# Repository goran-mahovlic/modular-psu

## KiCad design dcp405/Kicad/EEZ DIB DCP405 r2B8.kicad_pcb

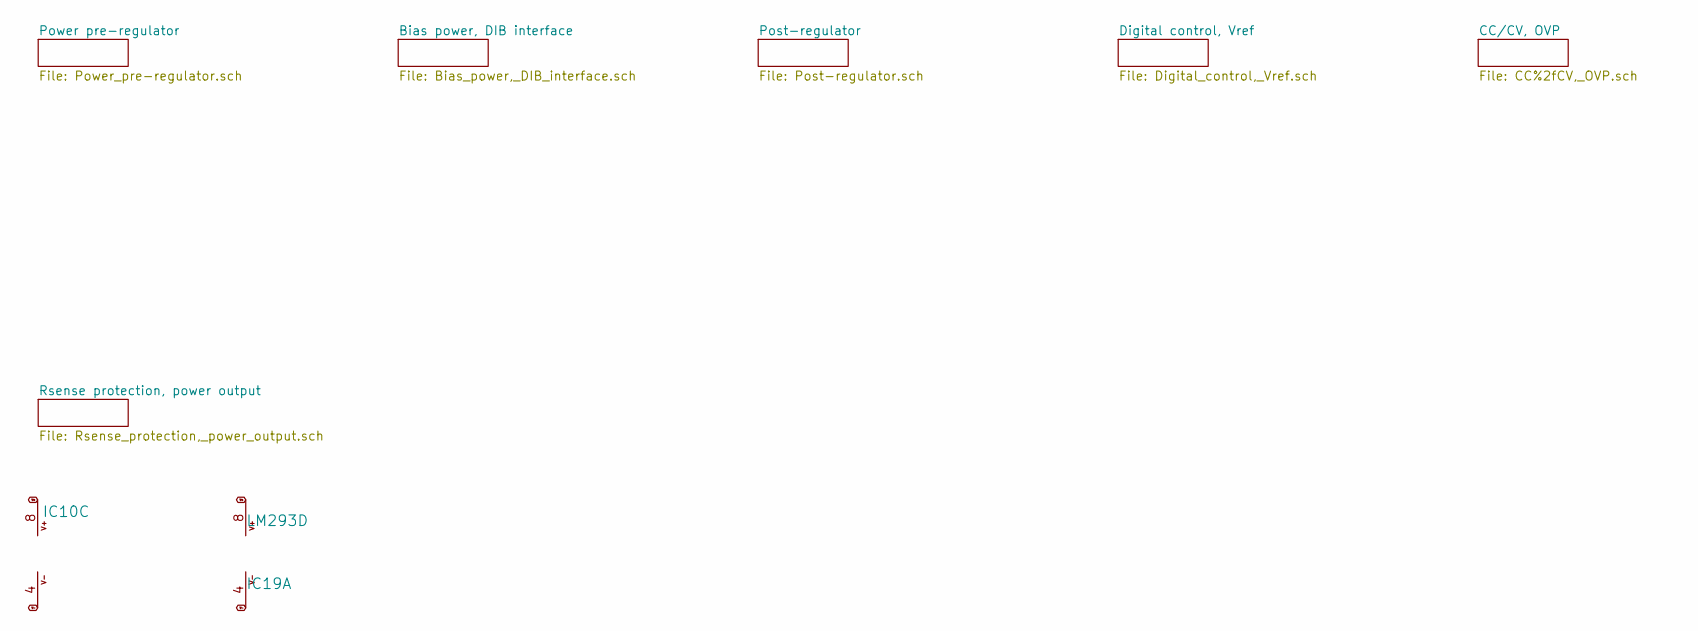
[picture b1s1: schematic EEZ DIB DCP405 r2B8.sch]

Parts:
IC10: MC33272ADR2G; SOIC127P600X173-8N
IC19: LM293D; SOIC127P600X173-8N

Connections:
V+: IC10.8 (V+), IC19.8 (V+); also elsewhere on the board
V-: IC10.4 (V-), IC19.4 (V-); also elsewhere on the board

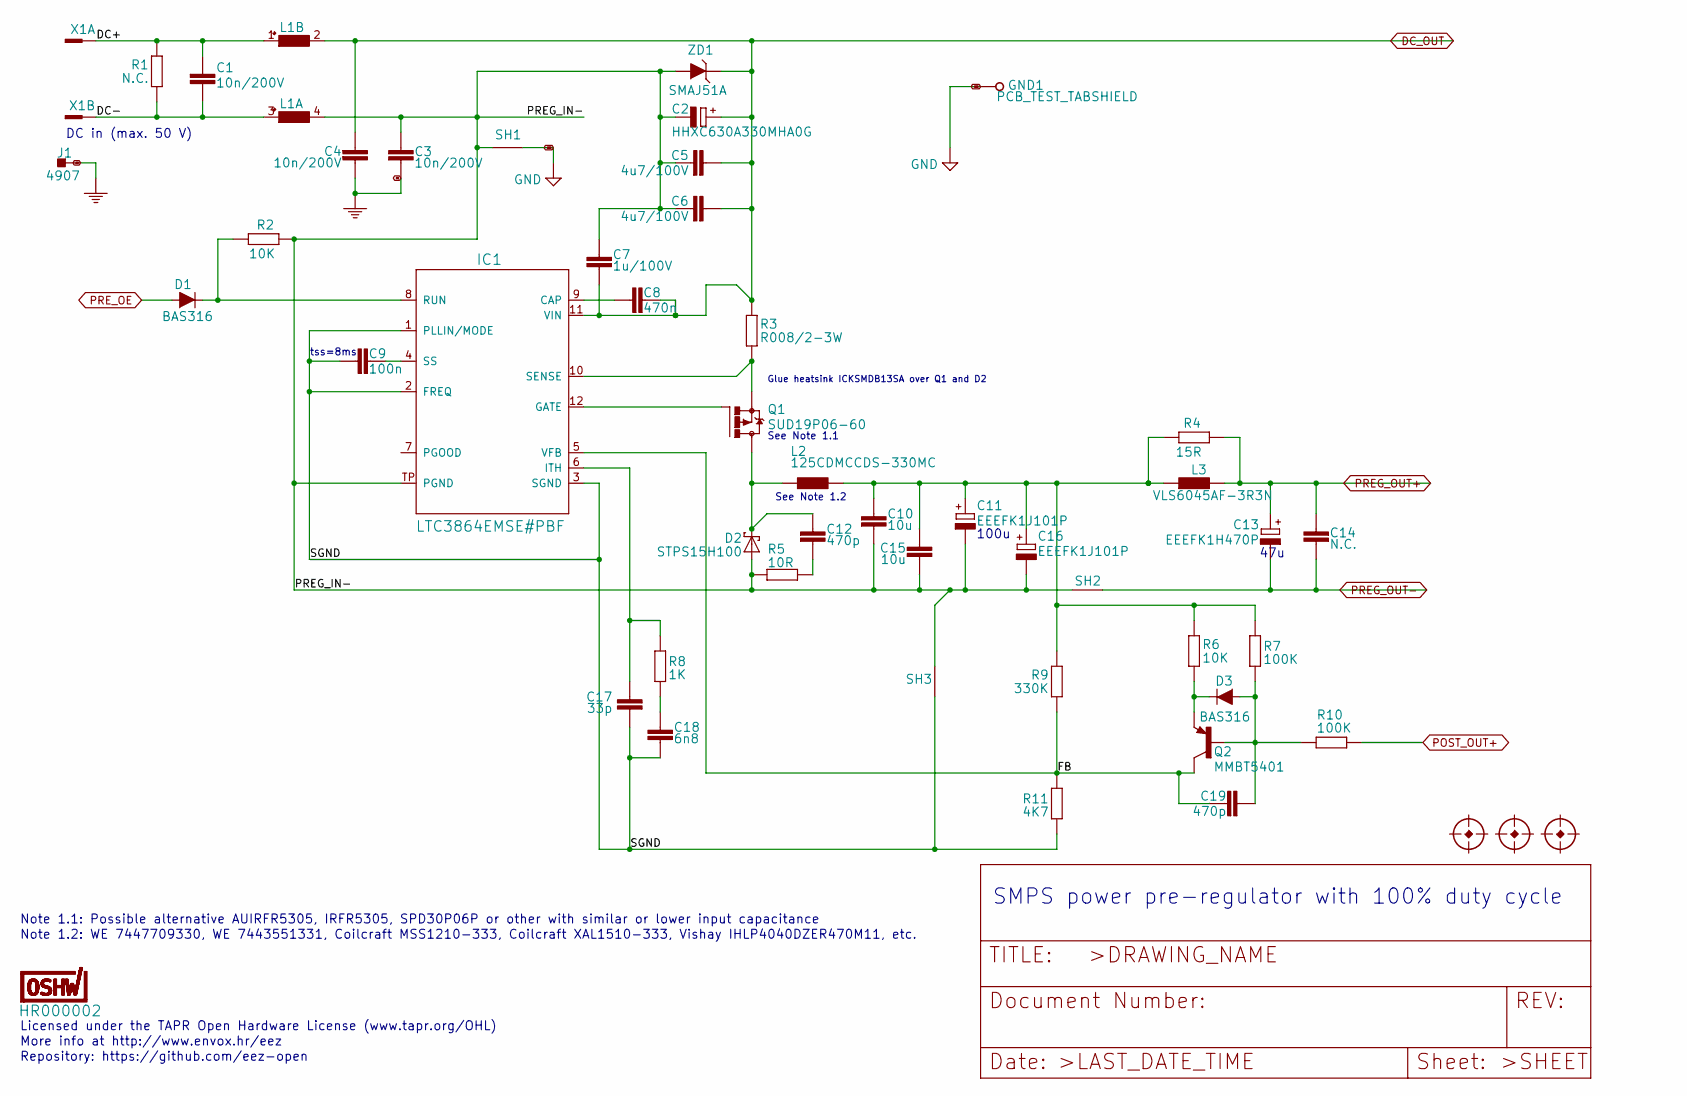
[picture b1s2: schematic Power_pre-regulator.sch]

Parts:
C1, C3, C4: 10n/200V; C1206
C2: HHXC630A330MHA0G; CAPAE830X1050N
C5, C6: 4u7/100V; C1210
C7: 1u/100V; C1206
C8: 470n; C0805
C9: 100n; C0603
C10, C15: 10u; C1210
C11, C16: EEEFK1J101P; CAPAE1030X1050N
C12, C19: 470p; C0805
C13: EEEFK1H470P; CAPAE830X1050N
C14: N.C.; C0805
C17: 33p; C0805
C18: 6n8; C0805
D1, D3: BAS316; SOD323-R
D2: STPS15H100; TO252-L
FM1, FM2, FM3: FIDUCIAL_2; FIDUCIAL_DUAL
GND: PCB_TEST_TABSHIELD; PCB_SHIELD_TAB
IC1: LTC3864EMSE#PBF; LTC_05-08-1666
J1: 4907; PCB_TAB-4907
L1: RN112-4-02-0M7; RN112
L2: 125CDMCCDS-330MC; 125CDMCC_DS
L3: VLS6045AF-3R3N; COILCRAFT_HPI0630
OSHWA: HR000002; CERT-SMALL-SILK
Q1: SUD19P06-60; TO229P990X239-3N
Q2: MMBT5401; SOT23-BEC
R1: N.C.; R2512
R2, R6: 10K; R0805
R3: R008/2-3W; R2512
R4: 15R; R2010
R5: 10R; R1206
R7, R10: 100K; R0805
R8: 1K; R0805
R9: 330K; R0805
R11: 4K7; R0805
SH1: SHORTNOHOLE; SHORT_NOHOLE
SH2: Pgnd to Pout- short; SHORT_NOHOLE
SH3: Sgnd to Pgnd short; SHORT_NOHOLE
X1: 39-30-1020; MINIFIT_39301020
ZD1: SMAJ51A; DO214AA

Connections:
/Power pre-regulator/DC+: C1.2, L1.1, R1.2, X1.1
/Power pre-regulator/DC-: C1.1, L1.3 (1), R1.1, X1.2
/Power pre-regulator/FB: C19.1, IC1.5 (VFB), Q2.C, R9.2, R11.1
/Power pre-regulator/PREG_IN-: C2.-, C3.1, C5.2, C6.2, C7.2, C10.2, C11.-, C15.2, C16.-, D2.1 (A), D2.2 (A), IC1.TP (PGND), L1.4 (2), R2.1, R5.1, SH1.1 (GND_A), SH2.2 (GND_B), SH3.2 (GND_B), ZD1.A
/Power pre-regulator/SGND: C9.1, C17.2, C18.2, IC1.1 (PLLIN/MODE), IC1.2 (FREQ), IC1.3 (SGND), R11.2, SH3.1 (GND_A)
DC_OUT: C2.+, C4.2, C5.1, C6.1, C7.1, C8.2, IC1.11 (VIN), L1.2, R3.1, ZD1.C; also elsewhere on the board
GND: GND.1, SH1.2 (GND_B); also elsewhere on the board
unnamed: C8.1, IC1.9 (CAP)
unnamed: C9.2, IC1.4 (SS)
unnamed: C10.1, C11.+, C15.1, C16.+, L2.2, L3.1, R4.1, R6.1, R7.1, R9.1
unnamed: C12.1, D2.3 (C), L2.1, Q1.2 (D)
unnamed: C12.2, R5.2
unnamed: C17.1, IC1.6 (ITH), R8.2
unnamed: C18.1, R8.1
unnamed: C19.2, D3.A, Q2.B, R7.2, R10.1
unnamed: D1.C, IC1.8 (RUN), R2.2
unnamed: D3.C, Q2.E, R6.2
unnamed: IC1.10 (SENSE), Q1.3 (S), R3.2
unnamed: IC1.12 (GATE), Q1.1 (G)
PE: C3.2, C4.1, J1.1, J1.2; also elsewhere on the board
POST_OUT+: R10.2; also elsewhere on the board
PREG_OUT+: C13.+, C14.1, L3.2, R4.2; also elsewhere on the board
PREG_OUT-: C13.-, C14.2, SH2.1 (GND_A); also elsewhere on the board
PRE_OE: D1.A; also elsewhere on the board

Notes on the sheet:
47u
tss=8ms
Licensed under the TAPR Open Hardware License (www.tapr.org/OHL)
Repository: https://github.com/eez-open
More info at http://www.envox.hr/eez
SMPS power pre-regulator with 100% duty cycle
100u
See Note 1.1
Note 1.1: Possible alternative AUIRFR5305, IRFR5305, SPD30P06P or other with similar or lower input capacitance
Note 1.2: WE 7447709330, WE 7443551331, Coilcraft MSS1210-333, Coilcraft XAL1510-333, Vishay IHLP4040DZER470M11, etc.
DC in (max. 50 V)
See Note 1.2
Glue heatsink ICKSMDB13SA over Q1 and D2

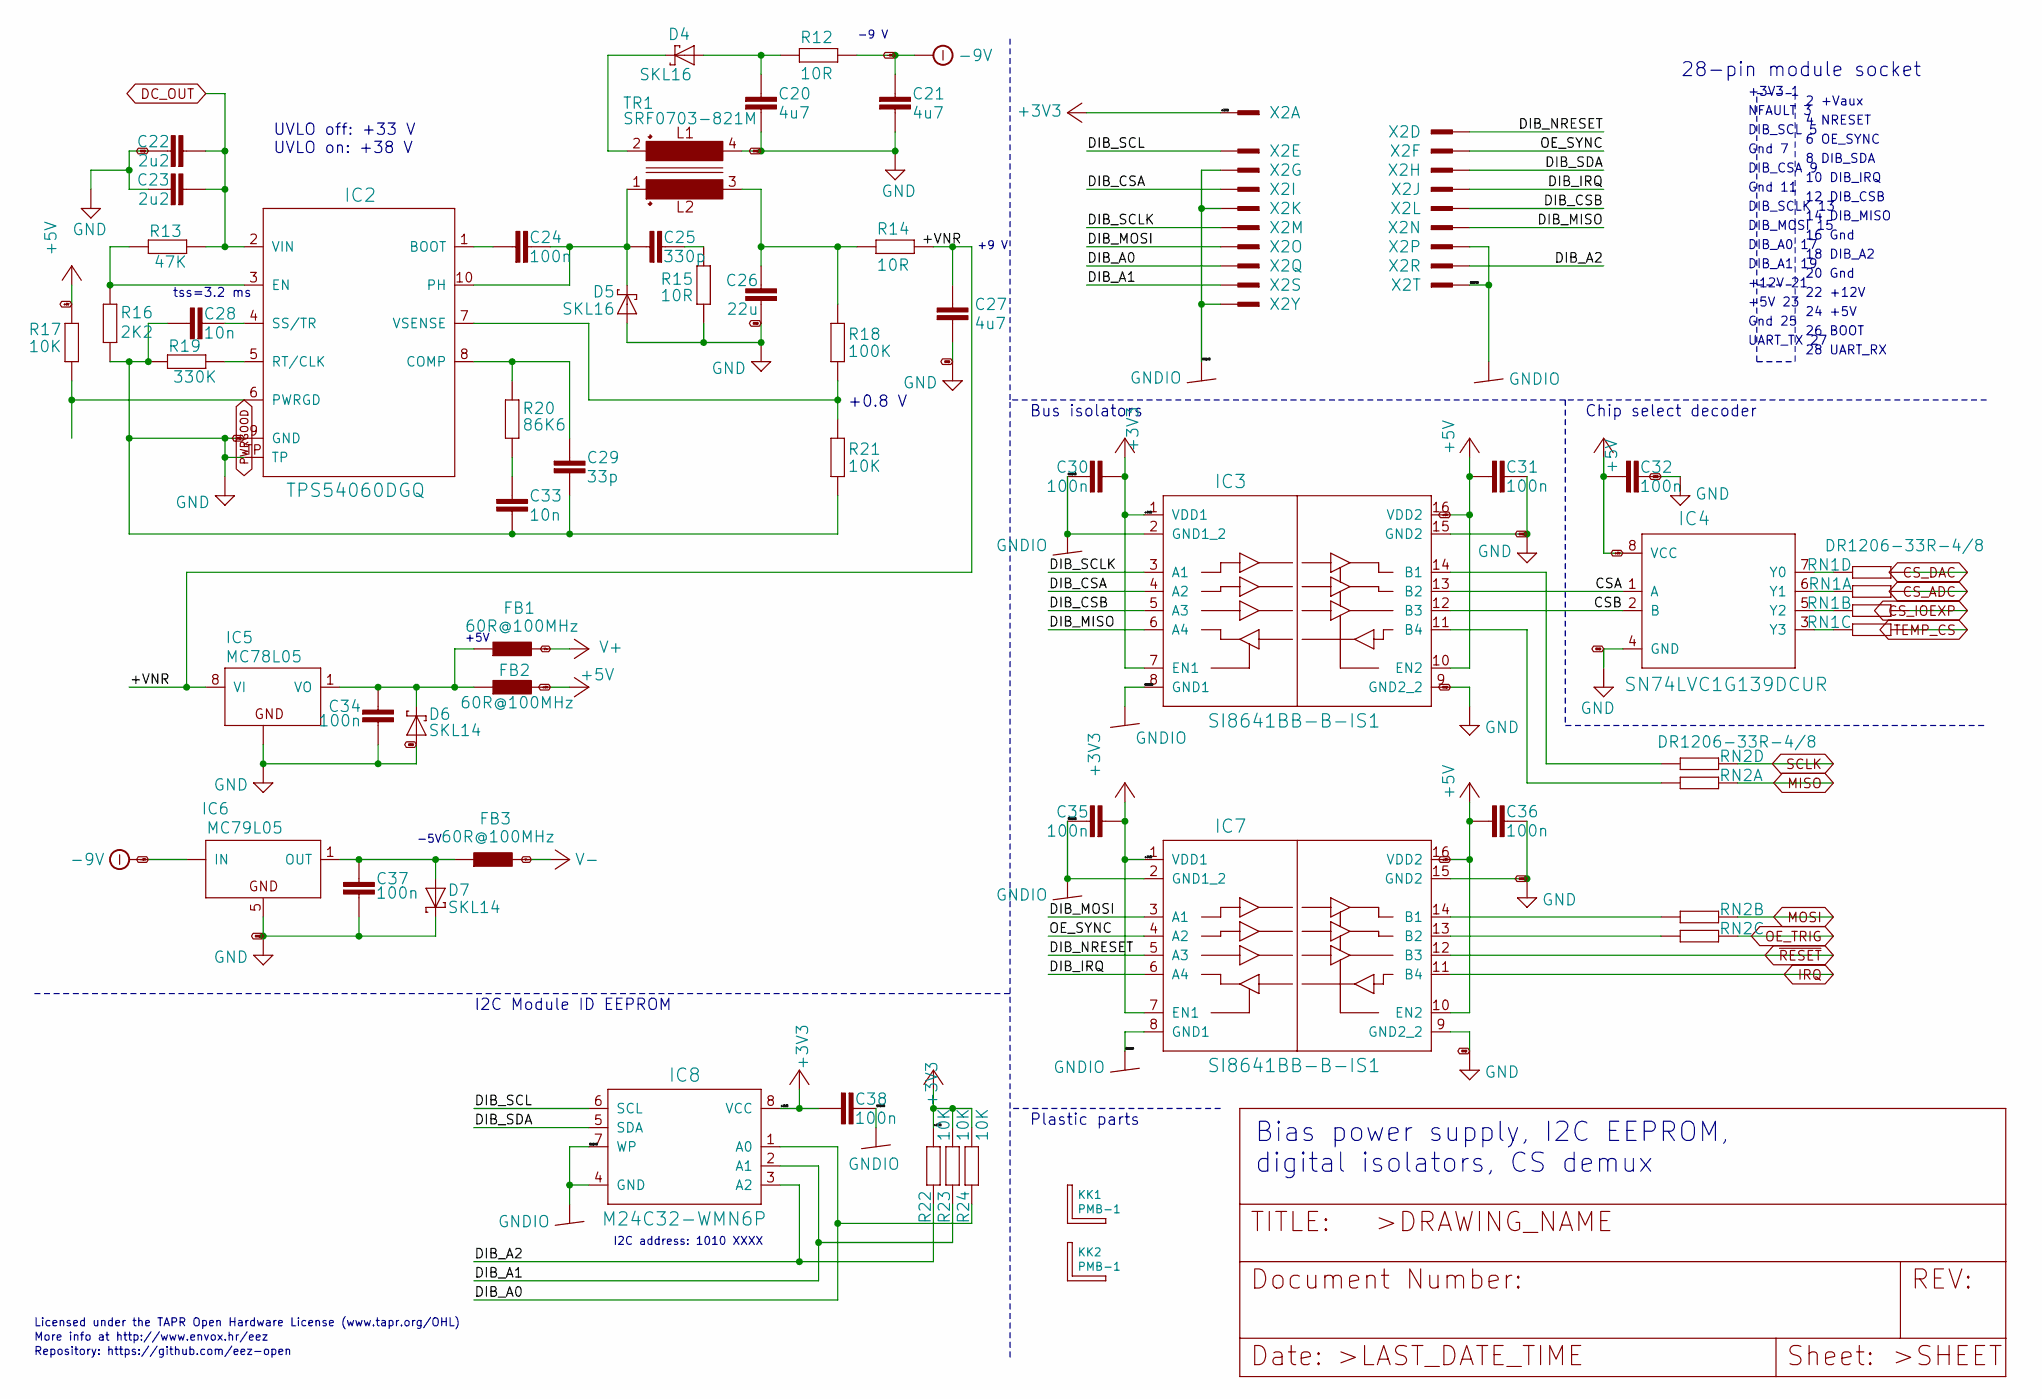
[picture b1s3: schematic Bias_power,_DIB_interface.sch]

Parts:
C20, C21, C27: 4u7; C1206
C22, C23: 2u2; C1206
C24, C30, C31, C32, C34, C35, C36, C37, C38: 100n; C0603
C25: 330p; C0805
C26: 22u; C1210
C28, C33: 10n; C0805
C29: 33p; C0805
D4, D5: SKL16; SOD123
D6, D7: SKL14; SOD123
FB1, FB2, FB3: 60R@100MHz; BEAD0603
IC2: TPS54060DGQ; SOP50P490X110-11N
IC3, IC7: SI8641BB-B-IS1; SOIC-16
IC4: SN74LVC1G139DCUR; DCU8
IC5: MC78L05; SOIC127P600X173-8N
IC6: MC79L05; SOIC127P600X173-8N
IC8: M24C32-WMN6P; SOIC127P600X173-8N
KK1, KK2: PMB-1; PCB-MB
R12, R14, R15: 10R; R1206
R13: 47K; R0805
R16: 2K2; R0805
R17, R21, R22, R23, R24: 10K; R0805
R18: 100K; R0805
R19: 330K; R0805
R20: 86K6; R0805
RN1, RN2: DR1206-33R-4/8; CAY16
TR1: SRF0703-821M; SRF0703
X2: 77317-104-20LF; 77317-104-28LF

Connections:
+3V3: C30.1, C35.1, C38.2, IC3.1 (VDD1), IC3.7 (EN1), IC7.1 (VDD1), IC7.7 (EN1), IC8.8 (VCC), R22.1, R23.1, R24.1, X2.1
+5V: C31.2, C32.1, C36.2, FB2.P$2 (2), IC3.10 (EN2), IC3.16 (VDD2), IC4.8 (VCC), IC7.10 (EN2), IC7.16 (VDD2), R17.1; also elsewhere on the board
-9V: C21.1, IC6.2 (IN), IC6.3 (IN), IC6.6 (IN), IC6.7 (IN), R12.1; also elsewhere on the board
/Bias power, DIB interface/+VNR: C27.1, IC5.8 (VI), R14.1
/Bias power, DIB interface/CSA: IC3.13 (B2), IC4.1 (A)
/Bias power, DIB interface/CSB: IC3.12 (B3), IC4.2 (B)
/Bias power, DIB interface/DIB_A0: IC8.1 (A0), R24.2, X2.17
/Bias power, DIB interface/DIB_A1: IC8.2 (A1), R23.2, X2.19
/Bias power, DIB interface/DIB_A2: IC8.3 (A2), R22.2, X2.18
/Bias power, DIB interface/DIB_CSA: IC3.4 (A2), X2.9
/Bias power, DIB interface/DIB_CSB: IC3.5 (A3), X2.12
/Bias power, DIB interface/DIB_IRQ: IC7.6 (A4), X2.10
/Bias power, DIB interface/DIB_MISO: IC3.6 (A4), X2.14
/Bias power, DIB interface/DIB_MOSI: IC7.3 (A1), X2.15
/Bias power, DIB interface/DIB_NRESET: IC7.5 (A3), X2.4
/Bias power, DIB interface/DIB_SCL: IC8.6 (SCL), X2.5
/Bias power, DIB interface/DIB_SCLK: IC3.3 (A1), X2.13
/Bias power, DIB interface/DIB_SDA: IC8.5 (SDA), X2.8
/Bias power, DIB interface/OE_SYNC: IC7.4 (A2), X2.6
CS_ADC: RN1.7 (2); also elsewhere on the board
CS_DAC: RN1.8 (2); also elsewhere on the board
CS_IOEXP: RN1.6 (2); also elsewhere on the board
DC_OUT: C22.1, C23.1, IC2.2 (VIN), R13.2; also elsewhere on the board
GND: C20.2, C21.2, C22.2, C23.2, C26.2, C27.2, C28.2, C29.1, C31.1, C32.2, C33.1, C34.2, C36.1, C37.1, D5.A, D6.A, D7.C, IC2.9 (GND), IC2.TP, IC3.9 (GND2_2), IC3.15 (GND2), IC4.4 (GND), IC5.2 (GND), IC5.3 (GND), IC5.6 (GND), IC5.7 (GND), IC6.5 (GND), IC7.9 (GND2_2), IC7.15 (GND2), R15.1, R16.1, R19.1, R21.1, TR1.4; also elsewhere on the board
GNDIO: C30.2, C35.2, C38.1, IC3.2 (GND1_2), IC3.8 (GND1), IC7.2 (GND1_2), IC7.8 (GND1), IC8.4 (GND), IC8.7 (WP), X2.7, X2.11, X2.16, X2.20, X2.25
IRQ: IC7.11 (B4); also elsewhere on the board
MISO: RN2.7 (2); also elsewhere on the board
MOSI: RN2.6 (2); also elsewhere on the board
unnamed: C20.1, D4.A, R12.2
unnamed: C24.1, C25.1, D5.C, IC2.10 (PH), TR1.1
unnamed: C24.2, IC2.1 (BOOT)
unnamed: C25.2, R15.2
unnamed: C26.1, R14.2, R18.2, TR1.3
unnamed: C28.1, IC2.4 (SS/TR)
unnamed: C29.2, IC2.8 (COMP), R20.2
unnamed: C33.2, R20.1
unnamed: C34.1, D6.C, FB1.P$1 (1), FB2.P$1 (1), IC5.1 (VO)
unnamed: C37.2, D7.A, FB3.P$1 (1), IC6.1 (OUT)
unnamed: D4.C, TR1.2
unnamed: IC2.3 (EN), R13.1, R16.2
unnamed: IC2.5 (RT/CLK), R19.2
unnamed: IC2.7 (VSENSE), R18.1, R21.2
unnamed: IC3.11 (B4), RN2.2 (1)
unnamed: IC3.14 (B1), RN2.1
unnamed: IC4.3 (Y3), RN1.4 (1)
unnamed: IC4.5 (Y2), RN1.3 (1)
unnamed: IC4.6 (Y1), RN1.2 (1)
unnamed: IC4.7 (Y0), RN1.1
unnamed: IC7.13 (B2), RN2.4 (1)
unnamed: IC7.14 (B1), RN2.3 (1)
OE_TRIG: RN2.5 (2); also elsewhere on the board
PWRGOOD: IC2.6 (PWRGD), R17.2; also elsewhere on the board
SCLK: RN2.8 (2); also elsewhere on the board
TEMP_CS: RN1.5 (2); also elsewhere on the board
V+: FB1.P$2 (2); also elsewhere on the board
V-: FB3.P$2 (2); also elsewhere on the board
~RESET: IC7.12 (B3); also elsewhere on the board

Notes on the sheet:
Licensed under the TAPR Open Hardware License (www.tapr.org/OHL)
Repository: https://github.com/eez-open
More info at http://www.envox.hr/eez
I2C Module ID EEPROM
Bus isolators
Bias power supply, I2C EEPROM, digital isolators, CS demux
Plastic parts
Chip select decoder
Gnd 7
22 +12V
16 Gnd
6 OE_SYNC
24 +5V
+5V 23
Gnd 25
28-pin module socket
+12V 21
10 DIB_IRQ
DIB_CSA 9
2 +Vaux
12 DIB_CSB
+3V3 1
Gnd 11
8 DIB_SDA
DIB_SCL 5
DIB_A1 19
4 NRESET
DIB_A0 17
20 Gnd
NFAULT 3
14 DIB_MISO
DIB_MOSI 15
DIB_SCLK 13
18 DIB_A2
-5V
+5V
I2C address: 1010 XXXX
+9 V
UVLO off: +33 V UVLO on: +38 V
+0.8 V

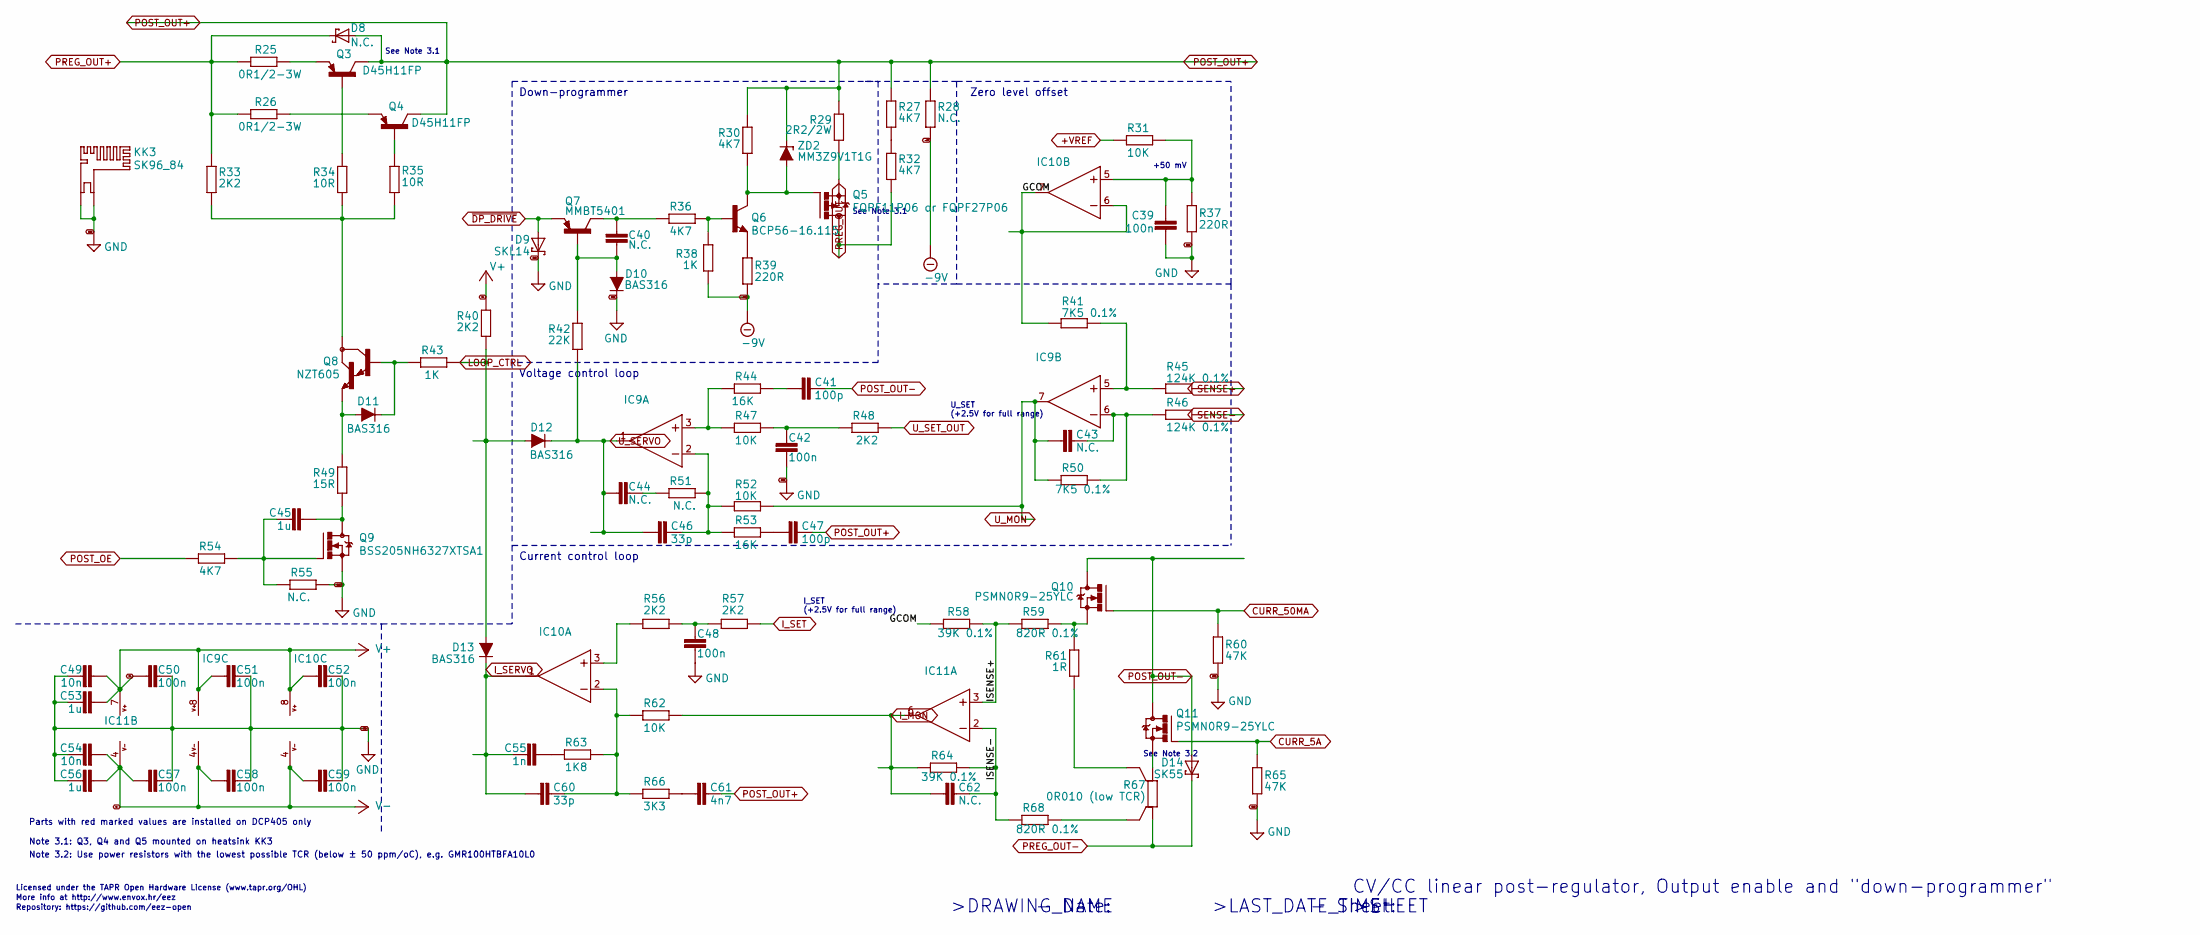
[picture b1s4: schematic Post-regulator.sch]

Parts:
C39, C42, C48, C50, C51, C52, C57, C58, C59: 100n; C0603
C40, C43, C44, C62: N.C.; C0805
C41, C47: 100p; C0805
C45, C53, C56: 1u; C0805
C46, C60: 33p; C0805
C49, C54: 10n; C0805
C55: 1n; C0805
C61: 4n7; C0805
D8: N.C.; SOD123
D9: SKL14; SOD123
D10, D11, D12, D13: BAS316; SOD323-R
D14: SK55; SMB
IC9: TL072D; SOIC127P600X173-8N
IC10: MC33272ADR2G; SOIC127P600X173-8N
IC11: LTC2050HVCS8#PBF; SOIC127P600X173-8N
KK3: SK96_84
Q3, Q4: D45H11FP; TO220FP-V
Q5: FQPF11P06 or FQPF27P06; TO220FP-V
Q6: BCP56-16.115; SOT230P700X180-4N
Q7: MMBT5401; SOT23-BEC
Q8: NZT605; SOT230P700X180-4N
Q9: BSS205NH6327XTSA1; SOT103P240X110-3N
Q10, Q11: PSMN0R9-25YLC; SOT669
R25, R26: 0R1/2-3W; R2512
R27, R30, R32, R36, R54: 4K7; R0805
R28, R51, R55: N.C.; R0805
R29: 2R2/2W; R2512
R31, R47, R52, R62: 10K; R0805
R33, R40, R48, R56, R57: 2K2; R0805
R34, R35: 10R; R1206
R37, R39: 220R; R0805
R38, R43: 1K; R0805
R41, R50: 7K5 0.1%; R0805
R42: 22K; R0805
R44, R53: 16K; R0805
R45, R46: 124K 0.1%; R0805
R49: 15R; R2010
R58, R64: 39K 0.1%; R0805
R59, R68: 820R 0.1%; R0805
R60, R65: 47K; R0805
R61: 1R; R1206
R63: 1K8; R0805
R66: 3K3; R0805
R67: 0R010 (low TCR); R_2512-4WIRE
ZD2: MM3Z9V1T1G; SOD323-R

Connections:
+VREF: R31.1; also elsewhere on the board
-9V: R28.1, R38.2, R39.2; also elsewhere on the board
/Post-regulator/GCOM: IC10.6 (-IN), IC10.7 (OUT), R41.1, R58.1
/Post-regulator/ISENSE+: IC11.3 (+IN), R58.2, R59.2
/Post-regulator/ISENSE-: C62.1, IC11.2 (-IN), R64.1, R68.2
CURR_5A: Q11.4 (G), R65.2; also elsewhere on the board
CURR_50MA: Q10.4 (G), R60.2; also elsewhere on the board
GND: C39.2, C42.2, C48.2, C49.1, C50.2, C51.1, C52.1, C53.1, C54.1, C56.1, C57.2, C58.1, C59.1, D9.C, D10.C, KK3.1, KK3.2, Q9.2 (S), R37.2, R55.1, R60.1, R65.1; also elsewhere on the board
I_MON: C62.2, IC11.6 (OUT), R62.1, R64.2; also elsewhere on the board
I_SERVO: C55.2, C60.2, D13.C, IC10.1 (OUT); also elsewhere on the board
I_SET: R57.1; also elsewhere on the board
LOOP_CTRL: D12.A, D13.A, R40.1, R43.1; also elsewhere on the board
unnamed: C39.1, IC10.5 (+IN), R31.2, R37.1
unnamed: C40.1, D10.A, Q7.B, R42.2
unnamed: C40.2, Q7.C, R36.2
unnamed: C41.2, R44.1
unnamed: C42.1, R47.1, R48.2
unnamed: C43.1, IC9.6 (-IN), R46.1, R50.2
unnamed: C44.1, R51.2
unnamed: C45.1, Q9.1 (G), R54.1, R55.2
unnamed: C45.2, Q9.3 (D), R49.1
unnamed: C46.1, IC9.2 (-IN), R51.1, R52.2, R53.2
unnamed: C47.2, R53.1
unnamed: C48.1, R56.1, R57.2
unnamed: C55.1, R63.1
unnamed: C60.1, IC10.2 (-IN), R62.2, R63.2, R66.2
unnamed: C61.2, R66.1
unnamed: D11.A, Q8.3 (E), R49.2
unnamed: D11.C, Q8.1 (B), R43.2
unnamed: IC9.3 (+IN), R44.2, R47.2
unnamed: IC9.5 (+IN), R41.2, R45.1
unnamed: IC10.3 (+IN), R56.2
unnamed: Q3.1 (B), R34.2
unnamed: Q3.3 (E), R25.2
unnamed: Q4.1 (B), R35.2
unnamed: Q4.3 (E), R26.2
unnamed: Q5.1 (G), Q6.2 (C), Q6.4 (C), R30.2, ZD2.A
unnamed: Q5.3 (S), R29.1
unnamed: Q6.1 (B), R36.1, R38.1
unnamed: Q6.3 (E), R39.1
unnamed: Q8.2 (C), Q8.4 (C), R33.1, R34.1, R35.1
unnamed: Q10.1 (S), Q10.2 (S), Q10.3 (S), R59.1, R61.1
unnamed: Q11.1 (S), Q11.2 (S), Q11.3 (S), R67.2
unnamed: R27.1, R32.2
unnamed: R61.2, R67.2S
unnamed: R67.1S, R68.1
POST_OE: R54.2; also elsewhere on the board
POST_OUT+: C47.1, C61.1, D8.A, Q3.2 (C), Q4.2 (C), R27.2, R28.2, R29.2, R30.1, ZD2.C; also elsewhere on the board
POST_OUT-: C41.1, D14.A, Q10.MB (D), Q11.MB (D); also elsewhere on the board
PREG_OUT+: D8.C, R25.1, R26.1, R33.2; also elsewhere on the board
PREG_OUT-: D14.C, Q5.2 (D), R32.1, R67.1; also elsewhere on the board
SENSE+: R45.2; also elsewhere on the board
SENSE-: R46.2; also elsewhere on the board
U_MON: C43.2, IC9.7 (OUT), R50.1, R52.1; also elsewhere on the board
U_SERVO: C44.2, C46.2, D12.C, IC9.1 (OUT), R42.1; also elsewhere on the board
U_SET_OUT: R48.1; also elsewhere on the board
V+: C49.2, C50.1, C51.2, C52.2, C53.2, IC9.8 (V+), IC10.8 (V+), IC11.7 (V+), R40.2; also elsewhere on the board
V-: C54.2, C56.2, C57.1, C58.2, C59.2, IC9.4 (V-), IC10.4 (V-), IC11.4 (V-); also elsewhere on the board
~DP_DRIVE: D9.A, Q7.E; also elsewhere on the board

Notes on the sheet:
Voltage control loop
U_SET (+2.5V for full range)
Note 3.1: Q3, Q4 and Q5 mounted on heatsink KK3
Down-programmer
Licensed under the TAPR Open Hardware License (www.tapr.org/OHL)
Repository: https://github.com/eez-open
More info at http://www.envox.hr/eez
+50 mV
See Note 3.1
I_SET (+2.5V for full range)
Zero level offset
Note 3.2: Use power resistors with the lowest possible TCR (below ± 50 ppm/oC), e.g. GMR100HTBFA10L0
CV/CC linear post-regulator, Output enable and "down-programmer"
See Note 3.2
>SHEET
- Sheet:
>DRAWING_NAME
>LAST_DATE_TIME
- Date:
Current control loop
Parts with red marked values are installed on DCP405 only

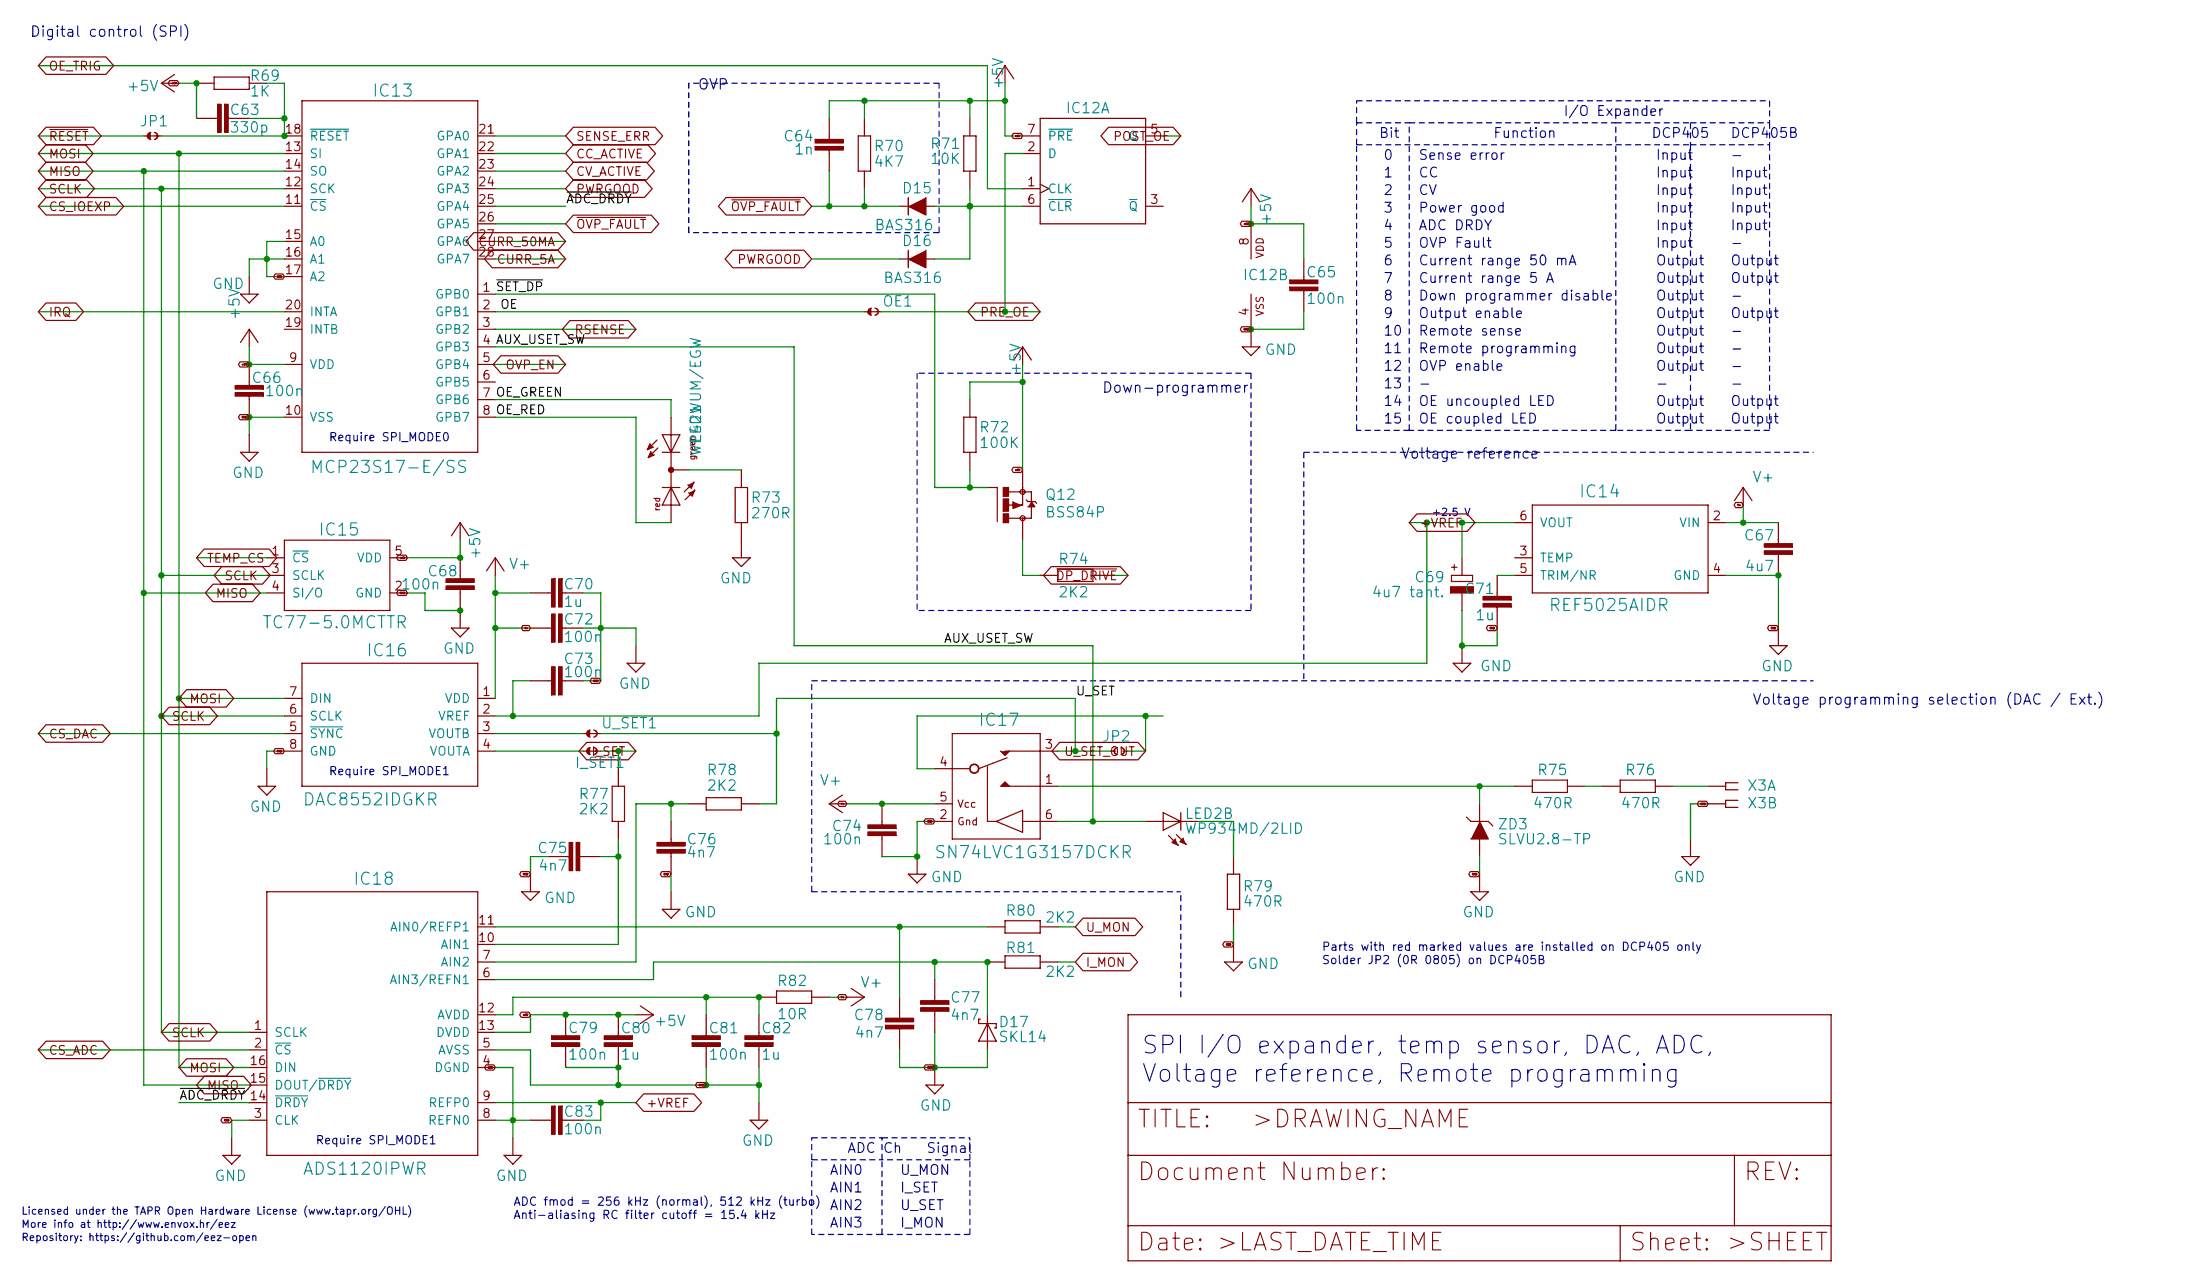
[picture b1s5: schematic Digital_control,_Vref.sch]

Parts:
C63: 330p; C0805
C64: 1n; C0805
C65, C66, C68, C72, C73, C74, C79, C81, C83: 100n; C0603
C67: 4u7; C1206
C69: 4u7 tant.; EC1206
C70, C71, C80, C82: 1u; C0805
C75, C76, C77, C78: 4n7; C0805
D15, D16: BAS316; SOD323-R
D17: SKL14; SOD123
IC12: 74AUP1G74DC.125; DCU8
IC13: MCP23S17-E/SS; SOP65P780X200-28N
IC14: REF5025AIDR; SOIC127P600X175-8N
IC15: TC77-5.0MCTTR; SOT23-5
IC16: DAC8552IDGKR; DGK8-M
IC17: SN74LVC1G3157DCKR; SOT65P210X110-6N
IC18: ADS1120IPWR; PW(R-PDSO-G16)
I_SET: JP2-NOCUT
JP1: JP2-NOCUT
JP2: JP2-CUT-0805; R_0805
LED1: WP42WUM/EGW; L-42WUM-1EGWT
LED2: WP934MD/2LID; WP934MD
OE: JP2-NOCUT
Q12: BSS84P; SOT95P237X112-3N
R69: 1K; R0805
R70: 4K7; R0805
R71: 10K; R0805
R72: 100K; R0805
R73: 270R; R0805
R74, R77, R78, R80, R81: 2K2; R0805
R75, R76, R79: 470R; R0805
R82: 10R; R1206
U_SET: JP2-NOCUT
X3: 691322110005; MC1,5_5-G-3,5
ZD3: SLVU2.8-TP; SOT23

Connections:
+5V: C63.2, C64.2, C65.2, C66.1, C68.1, C79.2, C80.2, IC12.7 (~PRE), IC12.8 (VDD), IC13.9 (VDD), IC15.5 (VDD), IC18.13 (DVDD), Q12.2 (S), R69.1, R70.1, R71.1, R72.1; also elsewhere on the board
+VREF: C69.+, C73.2, C83.2, IC14.6 (VOUT), IC16.2 (VREF), IC18.9 (REFP0); also elsewhere on the board
/Digital control, Vref/AUX_USET_SW: IC13.4 (GPB3), IC17.6 (CTRL), LED2.BA (A)
/Digital control, Vref/OE: IC13.2 (GPB1), OE.1
/Digital control, Vref/OE_GREEN: IC13.7 (GPB6), LED1.GREEN (AG)
/Digital control, Vref/OE_RED: IC13.8 (GPB7), LED1.RED (AR)
/Digital control, Vref/U_SET: IC17.3 (NC), JP2.1, R78.1, U_SET.2
/Digital control, Vref/~ADC_DRDY: IC13.25 (GPA4), IC18.14 (~DRDY)
/Digital control, Vref/~SET_DP: IC13.1 (GPB0), Q12.1 (G), R72.2
CC_ACTIVE: IC13.22 (GPA1); also elsewhere on the board
CS_ADC: IC18.2 (~CS); also elsewhere on the board
CS_DAC: IC16.5 (~SYNC); also elsewhere on the board
CS_IOEXP: IC13.11 (~CS); also elsewhere on the board
CURR_5A: IC13.28 (GPA7); also elsewhere on the board
CURR_50MA: IC13.27 (GPA6); also elsewhere on the board
CV_ACTIVE: IC13.23 (GPA2); also elsewhere on the board
GND: C65.1, C66.2, C67.2, C68.2, C69.-, C70.2, C71.2, C72.1, C73.1, C74.2, C75.1, C76.1, C77.2, C78.1, C79.1, C80.1, C81.1, C82.1, C83.1, D17.A, IC12.4 (VSS), IC13.10 (VSS), IC13.15 (A0), IC13.16 (A1), IC13.17 (A2), IC14.4 (GND), IC15.2 (GND), IC16.8 (GND), IC17.2 (GND), IC18.3 (CLK), IC18.4 (DGND), IC18.5 (AVSS), IC18.8 (REFN0), R73.2, R79.1, X3.2, ZD3.1 (A), ZD3.2 (A); also elsewhere on the board
IRQ: IC13.20 (INTA); also elsewhere on the board
I_MON: R81.1; also elsewhere on the board
I_SET: I_SET.2, R77.1; also elsewhere on the board
MISO: IC13.14 (SO), IC15.4 (SI/O), IC18.15 (DOUT/~DRDY); also elsewhere on the board
MOSI: IC13.13 (SI), IC16.7 (DIN), IC18.16 (DIN); also elsewhere on the board
unnamed: C63.1, IC13.18 (~RESET), JP1.2, R69.2
unnamed: C71.1, IC14.5 (TRIM/NR)
unnamed: C75.2, IC18.10 (AIN1), R77.2
unnamed: C76.2, IC18.7 (AIN2), R78.2
unnamed: C77.1, D17.C, IC18.6 (AIN3/REFN1), R81.2
unnamed: C78.2, IC18.11 (AIN0/REFP1), R80.2
unnamed: C81.2, C82.2, IC18.12 (AVDD), R82.2
unnamed: D15.A, D16.A, IC12.6 (~CLR), R71.2
unnamed: IC16.3 (VOUTB), U_SET.1
unnamed: IC16.4 (VOUTA), I_SET.1
unnamed: IC17.1 (NO), R75.1, ZD3.3 (C)
unnamed: LED1.CC (C), R73.1
unnamed: LED2.BC (C), R79.2
unnamed: Q12.3 (D), R74.2
unnamed: R75.2, R76.1
unnamed: R76.2, X3.1
OE_TRIG: IC12.1 (CLK); also elsewhere on the board
OVP_EN: IC13.5 (GPB4); also elsewhere on the board
POST_OE: IC12.5 (Q); also elsewhere on the board
PRE_OE: IC12.2 (D), OE.2; also elsewhere on the board
PWRGOOD: D16.C, IC13.24 (GPA3); also elsewhere on the board
RSENSE: IC13.3 (GPB2); also elsewhere on the board
SCLK: IC13.12 (SCK), IC15.3 (SCLK), IC16.6 (SCLK), IC18.1 (SCLK); also elsewhere on the board
SENSE_ERR: IC13.21 (GPA0); also elsewhere on the board
TEMP_CS: IC15.1 (~CS); also elsewhere on the board
U_MON: R80.1; also elsewhere on the board
U_SET_OUT: IC17.4 (COM), JP2.2; also elsewhere on the board
V+: C67.1, C70.1, C72.2, C74.1, IC14.2 (VIN), IC16.1 (VDD), IC17.5 (VDD), R82.1; also elsewhere on the board
~DP_DRIVE: R74.1; also elsewhere on the board
~OVP_FAULT: C64.1, D15.C, IC13.26 (GPA5), R70.2; also elsewhere on the board
~RESET: JP1.1; also elsewhere on the board

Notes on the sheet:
Require SPI_MODE1
Digital control (SPI)
Voltage reference
Licensed under the TAPR Open Hardware License (www.tapr.org/OHL)
Repository: https://github.com/eez-open
More info at http://www.envox.hr/eez
Function
DCP405
Sense error
Input
Bit
Down programmer disable
Remote sense
Remote programming
Power good
Output enable
Output
I/O Expander
SPI I/O expander, temp sensor, DAC, ADC, Voltage reference, Remote programming
Require SPI_MODE0
Current range 5 A
Current range 50 mA
+2.5 V
OE coupled LED
AIN0
AIN1
Signal
U_MON
I_SET
ADC Ch
U_SET
AIN2
AIN3
I_MON
Voltage programming selection (DAC / Ext.)
OE uncoupled LED
OVP enable
ADC DRDY
OVP Fault
ADC fmod = 256 kHz (normal), 512 kHz (turbo) Anti-aliasing RC filter cutoff = 15.4 kHz
